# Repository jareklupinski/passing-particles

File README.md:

# passing-particles
A simple device to display the current Background Radiation Level in a fun and interesting way!

This is a proof of concept device. It measures the Alpha, Beta, and Gamma particles (if available) currently present in the area occupied by the attached Geigar Tube.

Schematic:

Board Layout:

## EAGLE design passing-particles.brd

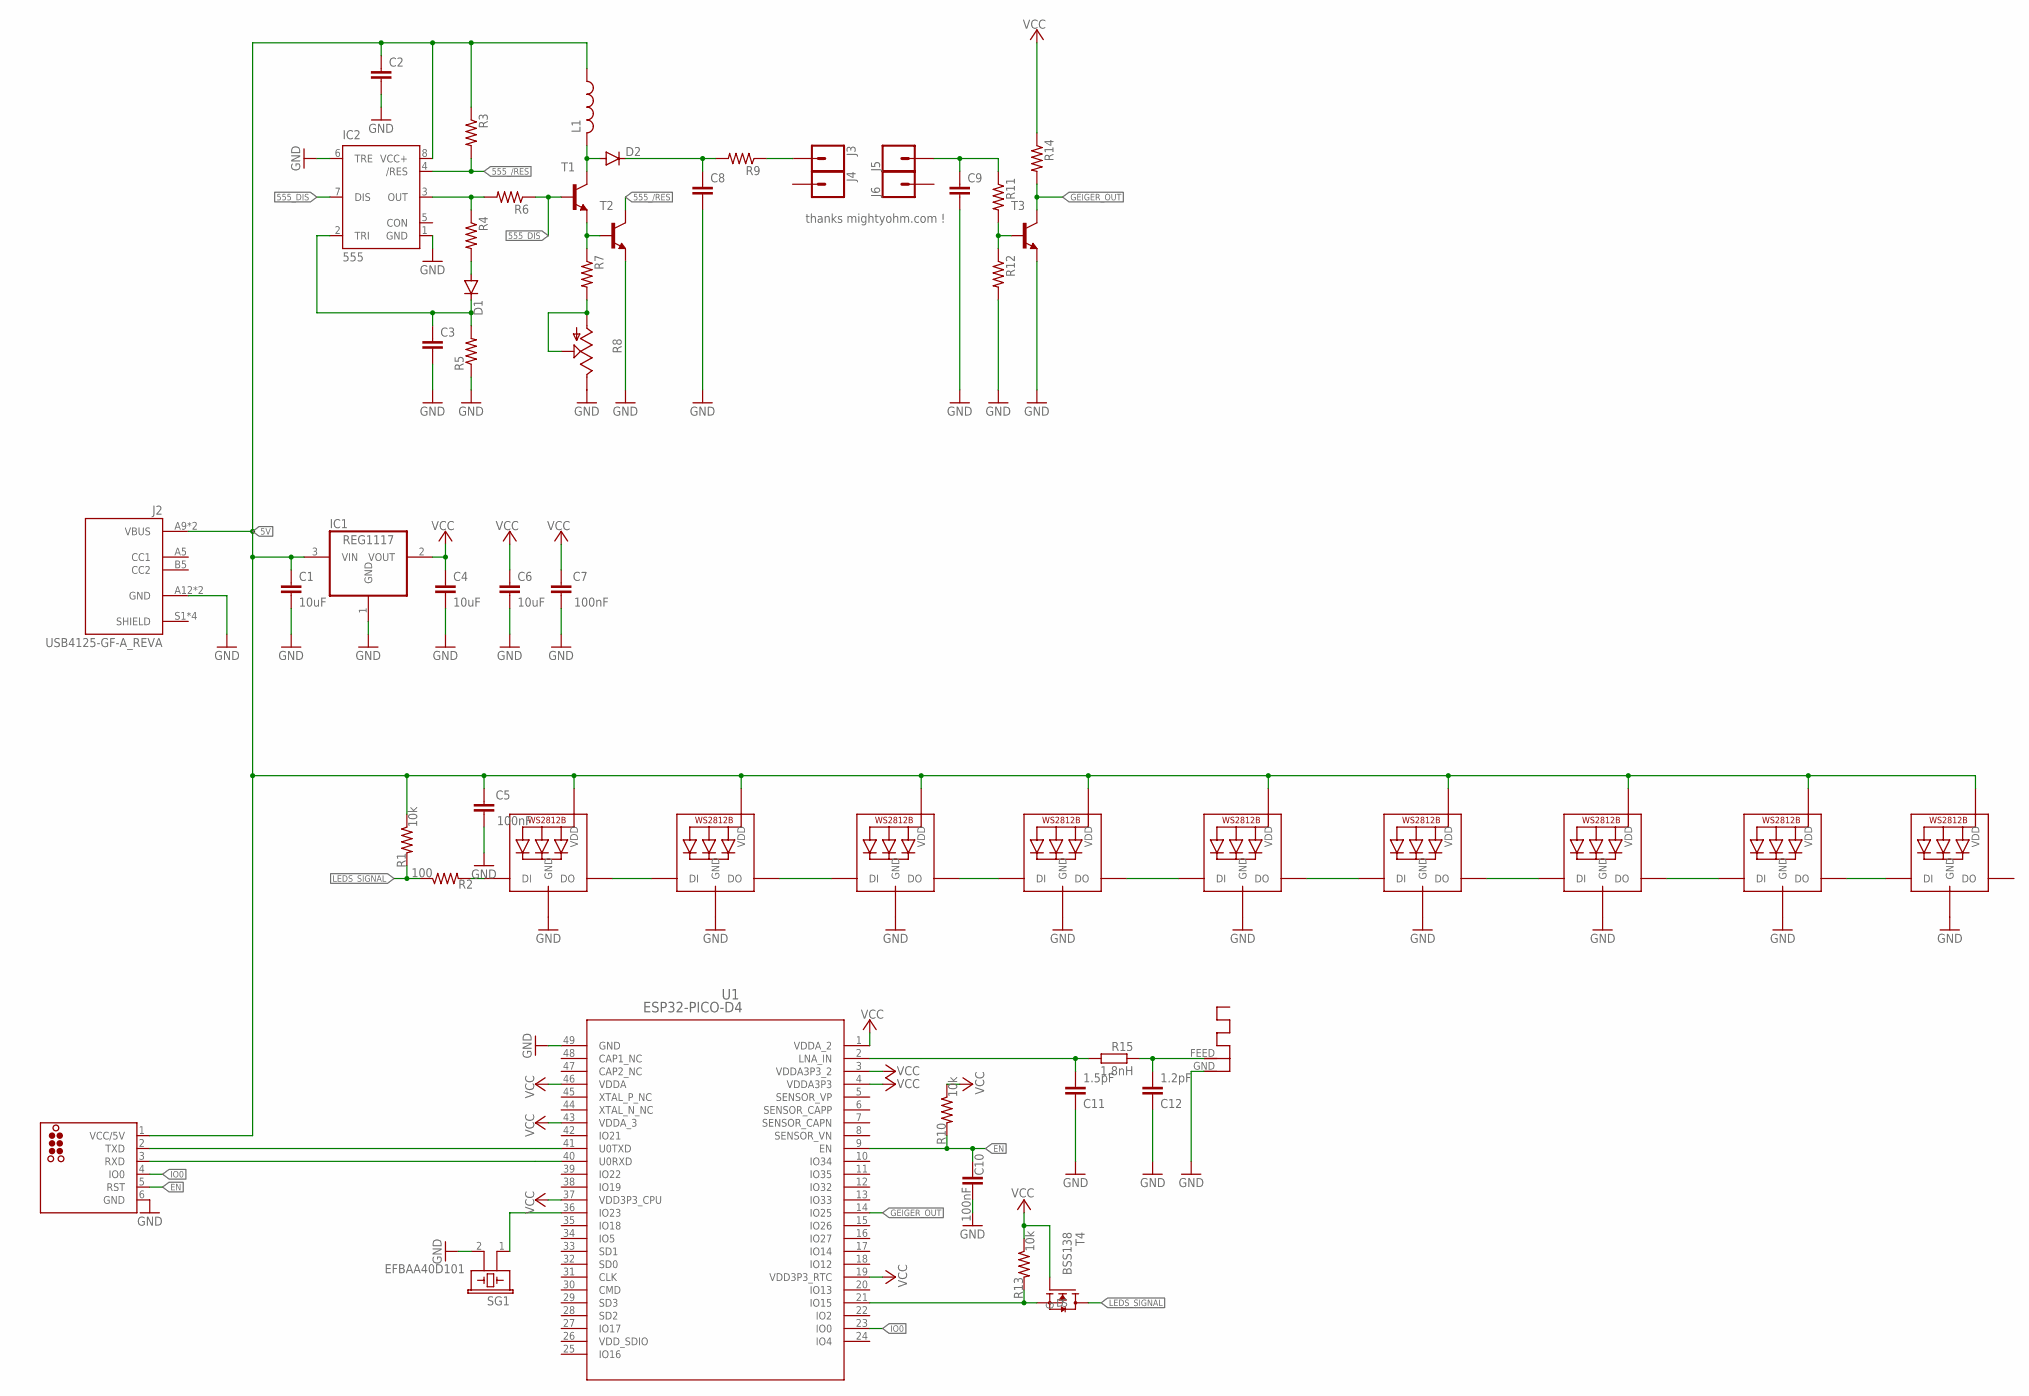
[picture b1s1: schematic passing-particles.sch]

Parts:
ANT1: ANTENNA; RN-ANT
C1, C4, C6: 10uF; C0805
C2, C3, C9: C-EUC0402; C0402
C5, C7, C10: 100nF; C0402
C8: C-EUC0805; C0805
C11: 1.5pF; C0402
C12: 1.2pF; C0402
D1, D2: DIODE-DO214AA; DO214AA
IC1: REG1117; SOT223
IC2: 555; SO08
J1: TC2030-ESP; TC2030-MCP
J2: USB4125-GF-A_REVA; GCT_USB4125-GF-A_REVA
J3, J4, J5, J6: CONN_01; 1X01
L1: L-USL2012C; L2012C
LED1, LED2, LED3, LED4, LED5, LED6, LED7, LED8, LED9: WS2812B5050; WS2812B
R1, R10, R13: 10k; R0402
R2: 100; R0402
R3, R4, R5, R6, R7, R9, R11, R12, R14: R-US_R0402; R0402
R8: TRIM_US-SM-42/43B; SM-42/43B
R15: 1.8nH; R0402
SG1: EFBAA40D101
T1, T2, T3: BC817-NPN-SOT23-BEC; SOT23-BEC
T4: BSS138
U1: ESP32-PICO-D4; ESP32-PICO-D4_EXP

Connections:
5V: C1.1, C2.1, C5.1, IC1.3 (VIN), IC2.8 (VCC+), J1.1 (VCC/5V), J2.A9 (VBUS), J2.B9 (VBUS), L1.1, LED1.1-VDD (VDD), LED2.1-VDD (VDD), LED3.1-VDD (VDD), LED4.1-VDD (VDD), LED5.1-VDD (VDD), LED6.1-VDD (VDD), LED7.1-VDD (VDD), LED8.1-VDD (VDD), LED9.1-VDD (VDD), R1.1, R3.1
555_/RES: IC2.4 (/RES), R3.2, T2.C
555_DIS: IC2.7 (DIS), R6.1, T1.B
EN: C10.2, J1.5 (RST), R10.2, U1.9 (EN)
GEIGER_OUT: R14.2, T3.C, U1.14 (IO25)
GND: ANT1.GND, C1.2, C2.2, C3.2, C4.2, C5.2, C6.2, C7.2, C8.2, C9.2, C10.1, C11.1, C12.1, IC1.1 (GND), IC2.1 (GND), IC2.6 (TRE), J1.6 (GND), J2.A12 (GND), J2.B12 (GND), LED1.3-GND (GND), LED2.3-GND (GND), LED3.3-GND (GND), LED4.3-GND (GND), LED5.3-GND (GND), LED6.3-GND (GND), LED7.3-GND (GND), LED8.3-GND (GND), LED9.3-GND (GND), R5.1, R8.3 (E), R12.2, SG1.2, T2.E, T3.E, U1.49 (GND)
IO0: J1.4 (IO0), U1.23 (IO0)
LEDS_SIGNAL: R1.2, R2.1, T4.D
unnamed: IC2.3 (OUT), R4.1, R6.2
unnamed: D1.A, R4.2
unnamed: C3.1, D1.C, IC2.2 (TRI), R5.2
unnamed: R7.1, T1.E, T2.B
unnamed: D2.A, L1.2, T1.C
unnamed: R7.2, R8.1 (A), R8.2 (S)
unnamed: C8.1, D2.C, R9.2
unnamed: J3.1, R9.1
unnamed: C9.1, J5.1, R11.1
unnamed: R11.2, R12.1, T3.B
unnamed: ANT1.FEED, C12.2, R15.1
unnamed: LED1.2-DOUT (DO), LED2.4-DIN (DI)
unnamed: C11.2, R15.2, U1.2 (LNA_IN)
unnamed: J1.2 (TXD), U1.41 (U0TXD)
unnamed: LED2.2-DOUT (DO), LED3.4-DIN (DI)
unnamed: LED3.2-DOUT (DO), LED4.4-DIN (DI)
unnamed: LED4.2-DOUT (DO), LED5.4-DIN (DI)
unnamed: LED5.2-DOUT (DO), LED6.4-DIN (DI)
unnamed: LED6.2-DOUT (DO), LED7.4-DIN (DI)
unnamed: LED7.2-DOUT (DO), LED8.4-DIN (DI)
unnamed: LED8.2-DOUT (DO), LED9.4-DIN (DI)
unnamed: R13.2, T4.S, U1.21 (IO15)
unnamed: SG1.1, U1.36 (IO23)
unnamed: LED1.4-DIN (DI), R2.2
unnamed: J1.3 (RXD), U1.40 (U0RXD)
VCC: C4.1, C6.1, C7.1, IC1.2 (VOUT), R10.1, R13.1, R14.1, T4.G, U1.1 (VDDA_2), U1.3 (VDDA3P3_2), U1.4 (VDDA3P3), U1.19 (VDD3P3_RTC), U1.37 (VDD3P3_CPU), U1.43 (VDDA_3), U1.46 (VDDA)
VDD_SDIO: U1.26 (VDD_SDIO)

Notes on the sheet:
thanks mightyohm.com !

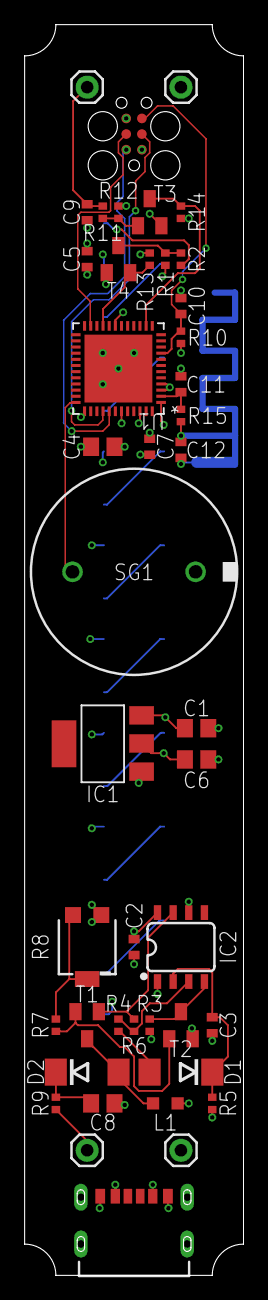
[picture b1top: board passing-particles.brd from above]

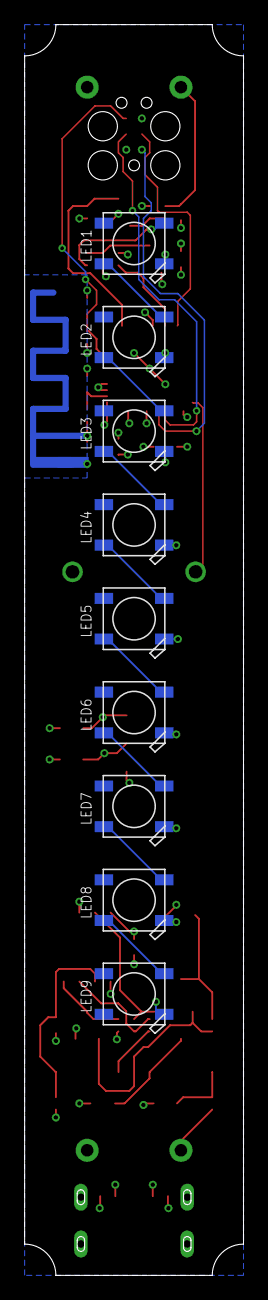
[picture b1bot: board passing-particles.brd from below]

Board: 4 copper layers, 17.8 x 101.6 mm, 54 parts (10 on the bottom side), 34 nets.

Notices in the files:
parts and their libraries:
SparkFun-IC-Special-Function: Licensing: Creative Commons ShareAlike 4.0 International - https://creativecommons.org/licenses/by-sa/4.0
tag-connect: ©2009 ROFA.cz - modified and updated by Robert Darlington ‹rdarlington@gmail.com›
